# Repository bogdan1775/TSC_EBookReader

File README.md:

### Croitoru Constantin-Bogdan 334CA
# Proiect TSC

## Diagrama Bloc

## Bill Of Materials
| Nume | Link componenta | Link Datasheet |
|----------------|----------------|----------------|		
|	BOOT_BUTTON	|	https://www.snapeda.com/parts/EVQP7L01P/Panasonic/view-part/?welcome=home&ref=search&t=evqp7l01p	|	https://industry.panasonic.com/global/en/downloads?tab=catalog&small_g_cd=203&part_no=EVQPUJ02K	|
|	C1	|	https://componentsearchengine.com/part-view/CC0402MRX5R5BB106/YAGEO	|	https://componentsearchengine.com/Datasheets/2/CC0402MRX5R5BB106.pdf	|
|	C1_BAT	|	https://componentsearchengine.com/part-view/CC0402MRX5R5BB106/YAGEO	|	https://componentsearchengine.com/Datasheets/2/CC0402MRX5R5BB106.pdf	|
|	C1_BAT1	|	https://www.snapeda.com/parts/CC0402DRNPO9BN5R1/Yageo/view-part/?ref=dk&t=LTSPICE_CC0402&con_ref=None	|	https://s3.amazonaws.com/snapeda/datasheet/CC0402DRNPO9BN5R1_Yageo.pdf	|
|	C2_BAT1	|	https://www.snapeda.com/parts/CC0402DRNPO9BN5R1/Yageo/view-part/?ref=dk&t=LTSPICE_CC0402&con_ref=None	|	https://s3.amazonaws.com/snapeda/datasheet/CC0402DRNPO9BN5R1_Yageo.pdf	|
|	C1_BAT2	| https://www.snapeda.com/parts/CC0402DRNPO9BN5R1/Yageo/view-part/?ref=dk&t=LTSPICE_CC0402&con_ref=None	|	https://s3.amazonaws.com/snapeda/datasheet/CC0402DRNPO9BN5R1_Yageo.pdf	|
|	C2	|	https://componentsearchengine.com/part-view/CC0402MRX5R5BB106/YAGEO	|	https://componentsearchengine.com/Datasheets/2/CC0402MRX5R5BB106.pdf	|
|	C2_BAT	|	https://componentsearchengine.com/part-view/CC0402MRX5R5BB106/YAGEO	|	https://componentsearchengine.com/Datasheets/2/CC0402MRX5R5BB106.pdf	|
|	C3	|	https://componentsearchengine.com/part-view/T491B107M006AT/KEMET	|	https://s3.amazonaws.com/snapeda/datasheet/TAJB475K025RNJ_AVX.pdf	|
|	C4	|	https://componentsearchengine.com/part-view/CC0402MRX5R5BB106/YAGEO	|	https://componentsearchengine.com/Datasheets/2/CC0402MRX5R5BB106.pdf	|
|	C4_USB	|	https://componentsearchengine.com/part-view/CC0402MRX5R5BB106/YAGEO	|	https://componentsearchengine.com/Datasheets/2/CC0402MRX5R5BB106.pdf	|
|	C5	|	https://componentsearchengine.com/part-view/CC0402MRX5R5BB106/YAGEO	|	https://componentsearchengine.com/Datasheets/2/CC0402MRX5R5BB106.pdf	|
|	C5_USB	|	https://componentsearchengine.com/part-view/CC0402MRX5R5BB106/YAGEO	|	https://componentsearchengine.com/Datasheets/2/CC0402MRX5R5BB106.pdf	|
|	C6	|	https://componentsearchengine.com/part-view/CC0402MRX5R5BB106/YAGEO	|	https://componentsearchengine.com/Datasheets/2/CC0402MRX5R5BB106.pdf	|
|	C7	|	https://componentsearchengine.com/part-view/CC0402MRX5R5BB106/YAGEO	|	https://componentsearchengine.com/Datasheets/2/CC0402MRX5R5BB106.pdf	|
|	C8	|	https://componentsearchengine.com/part-view/CC0402MRX5R5BB106/YAGEO	|	https://componentsearchengine.com/Datasheets/2/CC0402MRX5R5BB106.pdf	|
|	C9	|	https://www.snapeda.com/parts/CC0402DRNPO9BN5R1/Yageo/view-part/?ref=dk&t=LTSPICE_CC0402&con_ref=None	|	https://s3.amazonaws.com/snapeda/datasheet/CC0402DRNPO9BN5R1_Yageo.pdf	|
|	C10	|	https://componentsearchengine.com/part-view/CC0402MRX5R5BB106/YAGEO	|	https://componentsearchengine.com/Datasheets/2/CC0402MRX5R5BB106.pdf	|
|	C10_SUPERCAP	|	https://www.snapeda.com/parts/CPH3225A/Seiko+Instruments/view-part/?ref=eda	|	https://www.snapeda.com/parts/CPH3225A/Seiko%20Instruments/datasheet/	|
|	CHANGE_BUTTON	|	https://www.snapeda.com/parts/EVQP7L01P/Panasonic/view-part/?welcome=home&ref=search&t=evqp7l01p	|	https://industry.panasonic.com/global/en/downloads?tab=catalog&small_g_cd=203&part_no=EVQPUJ02K	|
|	CHG_LED	|	https://www.snapeda.com/parts/KP-1608SURCK/Kingbright/view-part/?ref=search&t=LED%200603	|	https://www.snapeda.com/parts/KP-1608SURCK/Kingbright/datasheet/	|
|	C_DELAY	|	https://componentsearchengine.com/part-view/CC0402MRX5R5BB106/YAGEO	|	https://componentsearchengine.com/Datasheets/2/CC0402MRX5R5BB106.pdf	|
|	D1	|	https://www.snapeda.com/parts/USBLC6-2SC6Y/STMicroelectronics/view-part/?ref=snap	|	https://www.snapeda.com/parts/USBLC6-2SC6Y/STMicroelectronics/datasheet/	|
|	D2	|	https://ro.mouser.com/ProductDetail/KYOCERA-AVX/SD0805S020S1R0?qs=jCA%252BPfw4LHbpkAoSnwrdjw%3D%3D	|	http://datasheets.avx.com/schottky.pdf	|
|	D3	|	https://www.snapeda.com/parts/MBR0530/Onsemi/view-part/?ref=eda	|	https://www.snapeda.com/parts/MBR0530/ON%20Semiconductor/datasheet/	|
|	D4	|	https://www.snapeda.com/parts/MBR0530/Onsemi/view-part/?ref=eda	|	https://www.snapeda.com/parts/MBR0530/ON%20Semiconductor/datasheet/	|
|	D5	|	https://www.snapeda.com/parts/MBR0530/Onsemi/view-part/?ref=eda	|	https://www.snapeda.com/parts/MBR0530/ON%20Semiconductor/datasheet/	|
|	D6	|	https://www.snapeda.com/parts/PGB1010603MR/Littelfuse/view-part/?ref=eda	|	https://www.snapeda.com/parts/PGB1010603MR/Littelfuse%20Inc./datasheet/	|
|	D7	|	https://ro.mouser.com/ProductDetail/KYOCERA-AVX/SD0805S020S1R0?qs=jCA%252BPfw4LHbpkAoSnwrdjw%3D%3D	|	http://datasheets.avx.com/schottky.pdf	|
|	D8	|	https://www.snapeda.com/parts/PGB1010603MR/Littelfuse/view-part/?ref=eda	|	https://www.snapeda.com/parts/PGB1010603MR/Littelfuse%20Inc./datasheet/	|
|	D9	|	https://www.snapeda.com/parts/PGB1010603MR/Littelfuse/view-part/?ref=eda	|	https://www.snapeda.com/parts/PGB1010603MR/Littelfuse%20Inc./datasheet/	|
|	D10	|	https://www.snapeda.com/parts/PGB1010603MR/Littelfuse/view-part/?ref=eda	|	https://www.snapeda.com/parts/PGB1010603MR/Littelfuse%20Inc./datasheet/	|
|	D11	|	https://www.snapeda.com/parts/PGB1010603MR/Littelfuse/view-part/?ref=eda	|	https://www.snapeda.com/parts/PGB1010603MR/Littelfuse%20Inc./datasheet/	|
|	D12	|	https://www.snapeda.com/parts/PGB1010603MR/Littelfuse/view-part/?ref=eda	|	https://www.snapeda.com/parts/PGB1010603MR/Littelfuse%20Inc./datasheet/	|
|	EPD_C1	|	https://componentsearchengine.com/part-view/CC0402MRX5R5BB106/YAGEO	|	https://componentsearchengine.com/Datasheets/2/CC0402MRX5R5BB106.pdf	|
|	EPD_C2	|	https://componentsearchengine.com/part-view/CC0402MRX5R5BB106/YAGEO	|	https://componentsearchengine.com/Datasheets/2/CC0402MRX5R5BB106.pdf	|
|	EPD_C5	|	https://componentsearchengine.com/part-view/CC0402MRX5R5BB106/YAGEO	|	https://componentsearchengine.com/Datasheets/2/CC0402MRX5R5BB106.pdf	|
|	EPD_C6	|	https://componentsearchengine.com/part-view/CC0402MRX5R5BB106/YAGEO	|	https://componentsearchengine.com/Datasheets/2/CC0402MRX5R5BB106.pdf	|
|	EPD_C7	|	https://componentsearchengine.com/part-view/CC0402MRX5R5BB106/YAGEO	|	https://componentsearchengine.com/Datasheets/2/CC0402MRX5R5BB106.pdf	|
|	EPD_C8	|	https://componentsearchengine.com/part-view/CC0402MRX5R5BB106/YAGEO	|	https://componentsearchengine.com/Datasheets/2/CC0402MRX5R5BB106.pdf	|
|	EPD_C9	|	https://componentsearchengine.com/part-view/CC0402MRX5R5BB106/YAGEO	|	https://componentsearchengine.com/Datasheets/2/CC0402MRX5R5BB106.pdf	|
|	EPD_C10	|	https://componentsearchengine.com/part-view/CC0402MRX5R5BB106/YAGEO	|	https://componentsearchengine.com/Datasheets/2/CC0402MRX5R5BB106.pdf	|
|	EPD_C11	|	https://componentsearchengine.com/part-view/CC0402MRX5R5BB106/YAGEO	|	https://componentsearchengine.com/Datasheets/2/CC0402MRX5R5BB106.pdf	|
|	EPD_C12	|	https://componentsearchengine.com/part-view/CC0402MRX5R5BB106/YAGEO	|	https://componentsearchengine.com/Datasheets/2/CC0402MRX5R5BB106.pdf	|
|	IC1	|	https://componentsearchengine.com/part-view/BD5229G-TR/ROHM%20Semiconductor	|	https://datasheet.datasheetarchive.com/originals/distributors/Datasheets_SAMA/f2b9741ef86007909f138d561a359946.pdf	|
|	IC4	|	https://componentsearchengine.com/part-view/XC6220A331MR-G/Torex	|	https://product.torexsemi.com/system/files/series/xc6220.pdf	|
|	J1	|	https://componentsearchengine.com/part-view/FH34SRJ-24S-0.5SH(99)/Hirose	|	https://www.hirose.com/en/product/document?clcode=CL0580-1255-6-99&productname=FH34SRJ-24S-0.5SH(99)&series=FH34SRJ&documenttype=2DDrawing&lang=en&documentid=0000990903	|
|	J2	|	https://componentsearchengine.com/part-view/USB4110-GF-A/GCT%20(GLOBAL%20CONNECTOR%20TECHNOLOGY)	|	https://gct.co/files/drawings/usb4110.pdf	|
|	J3	|	https://componentsearchengine.com/part-view/SM04B-SRSS-TB(LF)(SN)/JST%20(JAPAN%20SOLDERLESS%20TERMINALS)	| - |
|	J4	|	https://store.comet.srl.ro/Catalogue/Product/43497/	|	https://store.comet.srl.ro/Catalogue/Product/43497/	|
|	L1	|	https://ro.mouser.com/ProductDetail/Wurth-Elektronik/744043680?qs=PGXP4M47uW6VkZq%252BkzjrHA%3D%3D	|	https://www.we-online.com/components/products/datasheet/744043680.pdf	|
|	PFMF.050.1	|	https://ro.mouser.com/ProductDetail/EPCOS-TDK/B72520T0350K062?qs=dEfas%2FXlABIszF52uu7vrg%3D%3D	|	https://www.mouser.co.uk/ProductDetail/EPCOS-TDK/B72520T0350K062?qs=dEfas%2FXlABIszF52uu7vrg%3D%3D	|
|	Q1	|	https://componentsearchengine.com/part-view/DMG2305UX-7/Diodes%20Incorporated	|	https://www.diodes.com//assets/Datasheets/DMG2305UX.pdf	|
|	Q2	|	https://componentsearchengine.com/part-view/DMG2305UX-7/Diodes%20Incorporated	|	https://www.diodes.com//assets/Datasheets/DMG2305UX.pdf	|
|	Q3	|	https://componentsearchengine.com/part-view/SI1308EDL-T1-GE3/Vishay	|	https://componentsearchengine.com/Datasheets/1/SI1308EDL-T1-GE3.pdf	|
|	R1	|	https://componentsearchengine.com/part-view/R0402%201%25%20100%20K%20(RC0402FR-07100KL)/YAGEO	|	https://www.yageo.com/upload/media/product/products/datasheet/rchip/PYu-RC_Group_51_RoHS_L_12.pdf	|
|	R1-PINH	|	https://componentsearchengine.com/part-view/R0402%201%25%20100%20K%20(RC0402FR-07100KL)/YAGEO	|	https://www.yageo.com/upload/media/product/products/datasheet/rchip/PYu-RC_Group_51_RoHS_L_12.pdf	|
|	R1-PINH1	|	https://componentsearchengine.com/part-view/R0402%201%25%20100%20K%20(RC0402FR-07100KL)/YAGEO	|	https://www.yageo.com/upload/media/product/products/datasheet/rchip/PYu-RC_Group_51_RoHS_L_12.pdf	|
|	R1_BAT	|	https://componentsearchengine.com/part-view/R0402%201%25%20100%20K%20(RC0402FR-07100KL)/YAGEO	|	https://www.yageo.com/upload/media/product/products/datasheet/rchip/PYu-RC_Group_51_RoHS_L_12.pdf	|
|	R1_PWRUSB	|	https://componentsearchengine.com/part-view/R0402%201%25%20100%20K%20(RC0402FR-07100KL)/YAGEO	|	https://www.yageo.com/upload/media/product/products/datasheet/rchip/PYu-RC_Group_51_RoHS_L_12.pdf	|
|	R2	|	https://componentsearchengine.com/part-view/R0402%201%25%20100%20K%20(RC0402FR-07100KL)/YAGEO	|	https://www.yageo.com/upload/media/product/products/datasheet/rchip/PYu-RC_Group_51_RoHS_L_12.pdf	|
|	R2-PINH	|	https://componentsearchengine.com/part-view/R0402%201%25%20100%20K%20(RC0402FR-07100KL)/YAGEO	|	https://www.yageo.com/upload/media/product/products/datasheet/rchip/PYu-RC_Group_51_RoHS_L_12.pdf	|
|	R2-PINH1	|	https://componentsearchengine.com/part-view/R0402%201%25%20100%20K%20(RC0402FR-07100KL)/YAGEO	|	https://www.yageo.com/upload/media/product/products/datasheet/rchip/PYu-RC_Group_51_RoHS_L_12.pdf	|
|	R2-USB	|	https://componentsearchengine.com/part-view/R0402%201%25%20100%20K%20(RC0402FR-07100KL)/YAGEO	|	https://www.yageo.com/upload/media/product/products/datasheet/rchip/PYu-RC_Group_51_RoHS_L_12.pdf	|
|	R2-USB1	|	https://componentsearchengine.com/part-view/R0402%201%25%20100%20K%20(RC0402FR-07100KL)/YAGEO	|	https://www.yageo.com/upload/media/product/products/datasheet/rchip/PYu-RC_Group_51_RoHS_L_12.pdf	|
|	R2_BAT	|	https://componentsearchengine.com/part-view/R0402%201%25%20100%20K%20(RC0402FR-07100KL)/YAGEO	|	https://www.yageo.com/upload/media/product/products/datasheet/rchip/PYu-RC_Group_51_RoHS_L_12.pdf	|
|	R3	|	https://componentsearchengine.com/part-view/R0402%201%25%20100%20K%20(RC0402FR-07100KL)/YAGEO	|	https://www.yageo.com/upload/media/product/products/datasheet/rchip/PYu-RC_Group_51_RoHS_L_12.pdf	|
|	R4	|	https://componentsearchengine.com/part-view/R0402%201%25%20100%20K%20(RC0402FR-07100KL)/YAGEO	|	https://www.yageo.com/upload/media/product/products/datasheet/rchip/PYu-RC_Group_51_RoHS_L_12.pdf	|
|	R5	|	https://componentsearchengine.com/part-view/R0402%201%25%20100%20K%20(RC0402FR-07100KL)/YAGEO	|	https://www.yageo.com/upload/media/product/products/datasheet/rchip/PYu-RC_Group_51_RoHS_L_12.pdf	|
|	R6	|	https://componentsearchengine.com/part-view/R0402%201%25%20100%20K%20(RC0402FR-07100KL)/YAGEO	|	https://www.yageo.com/upload/media/product/products/datasheet/rchip/PYu-RC_Group_51_RoHS_L_12.pdf	|
|	R7	|	https://componentsearchengine.com/part-view/R0402%201%25%20100%20K%20(RC0402FR-07100KL)/YAGEO	|	https://www.yageo.com/upload/media/product/products/datasheet/rchip/PYu-RC_Group_51_RoHS_L_12.pdf	|
|	R8	|	https://componentsearchengine.com/part-view/R0402%201%25%20100%20K%20(RC0402FR-07100KL)/YAGEO	|	https://www.yageo.com/upload/media/product/products/datasheet/rchip/PYu-RC_Group_51_RoHS_L_12.pdf	|
|	R9	|	https://componentsearchengine.com/part-view/R0402%201%25%20100%20K%20(RC0402FR-07100KL)/YAGEO	|	https://www.yageo.com/upload/media/product/products/datasheet/rchip/PYu-RC_Group_51_RoHS_L_12.pdf	|
|	R10	|	https://componentsearchengine.com/part-view/R0402%201%25%20100%20K%20(RC0402FR-07100KL)/YAGEO	|	https://www.yageo.com/upload/media/product/products/datasheet/rchip/PYu-RC_Group_51_RoHS_L_12.pdf	|
|	RESET_BUTTON	|	https://www.snapeda.com/parts/EVQP7L01P/Panasonic/view-part/?welcome=home&ref=search&t=evqp7l01p	|	https://industry.panasonic.com/global/en/downloads?tab=catalog&small_g_cd=203&part_no=EVQPUJ02K	|
|	R_BOOT	|	https://componentsearchengine.com/part-view/R0402%201%25%20100%20K%20(RC0402FR-07100KL)/YAGEO	|	https://www.yageo.com/upload/media/product/products/datasheet/rchip/PYu-RC_Group_51_RoHS_L_12.pdf	|
|	R_CAPACITOR	|	https://componentsearchengine.com/part-view/R0402%201%25%20100%20K%20(RC0402FR-07100KL)/YAGEO	|	https://www.yageo.com/upload/media/product/products/datasheet/rchip/PYu-RC_Group_51_RoHS_L_12.pdf	|
|	R_CHANGE	|	https://componentsearchengine.com/part-view/R0402%201%25%20100%20K%20(RC0402FR-07100KL)/YAGEO	|	https://www.yageo.com/upload/media/product/products/datasheet/rchip/PYu-RC_Group_51_RoHS_L_12.pdf	|
|	R_CL1	|	https://componentsearchengine.com/part-view/R0402%201%25%20100%20K%20(RC0402FR-07100KL)/YAGEO	|	https://www.yageo.com/upload/media/product/products/datasheet/rchip/PYu-RC_Group_51_RoHS_L_12.pdf	|
|	R_RESET	|	https://componentsearchengine.com/part-view/R0402%201%25%20100%20K%20(RC0402FR-07100KL)/YAGEO	|	https://www.yageo.com/upload/media/product/products/datasheet/rchip/PYu-RC_Group_51_RoHS_L_12.pdf	|
|	SENSOR2	|	https://www.snapeda.com/parts/BME680/Bosch/view-part/?welcome=home	|	https://www.snapeda.com/parts/BME680/Bosch%20Sensortec/datasheet/	|
|	SJ1	|	https://grabcad.com/library/solder-jumpers-1	|	https://www.digikey.com/en/htmldatasheets/production/1809569/0/0/1/jumpers	|
|	U1	|	https://www.snapeda.com/parts/W25Q512JVEIQ/Winbond+Electronics/view-part/?ref=eda	|	https://www.snapeda.com/parts/W25Q512JVEIQ/Winbond%20Electronics/datasheet/	|
|	U2	|	https://www.snapeda.com/parts/ESP32-C6-WROOM-1-N8/Espressif+Systems/view-part/?ref=eda	|	https://www.snapeda.com/parts/ESP32-C6-WROOM-1-N8/Espressif%20Systems/datasheet/	|
|	U3	|	https://www.snapeda.com/parts/DS3231SN%23/Analog%20Devices/view-part/?ref=dk&t=DS3231SN%23&con_ref=None	|	https://www.snapeda.com/parts/DS3231SN%23/Analog%20Devices/datasheet/	|
|	U4	|	https://www.snapeda.com/parts/MAX17048G+T10/Analog+Devices/view-part/?ref=eda	|	https://www.snapeda.com/parts/MAX17048G+T10/Analog%20Devices/datasheet/	|
|	U5	|	https://ro.mouser.com/ProductDetail/Microchip-Technology/MCP73831T-2ACI-OT?qs=yUQqVecv4qvbBQBGbHx0Mw%3D%3D	|	https://ro.mouser.com/datasheet/2/268/MCP73831_Family_Data_Sheet_DS20001984H-3441711.pdf	|
|	TP1	|		|		|
|	TP2	|		|		|
|	TP3	|		|		|
|	TP4	|		|		|
|	TP5	|		|		|
|	TP6	|		|		|
|	TP7	|		|		|
|	TP8	|		|		|
|	TP9	|		|		|
|	TP10	|		|		|
|	TP11	|		|		|
|	TP12	|		|		|
|	TP13	|		|		|
|	TP14	|		|		|
|	TP15	|		|		|
|	TP16	|		|		|
|	TP17	|		|		|

## Descriere functionalitate
Dispozitivul este construit in jurul microcontrolerului ESP32-C6, care serveste ca unitate centrala de procesare si interactioneaza cu diverse componente esentiale pentru funcționarea sa.

Pentru a asigura o urmarire precisa a timpului, dispozitivul include un modul RTC DS3231SN, care comunica cu ESP32-C6 prin interfata I2C, garantand sincronizarea corecta a datelor si evenimentelor.

Senzorul de mediu BME680 este responsabil pentru colectarea informatiilor despre mediul înconjurator. Acesta transmite datele catre microcontroler prin I2C.

Dispozitivul beneficiaza si de un slot pentru card SD, utilizat pentru stocarea datelor colectate sau a altor informatii relevante. Acesta comunica cu ESP32-C6 prin interfata SPI, asigurand o stocare externa eficienta. De asemenea, exista o memorie Flash NOR externa de 64MB (W25Q512JVIQ) pentru stocarea firmware-ului si a altor date persistente.

Afisarea datelor si a altor informatii vizuale se realizeaza printr-un display E-Paper, care este conectat la ESP32-C6 prin pini GPIO dedicati.

In ceea ce priveste alimentarea, dispozitivul utilizeaza un conector USB-C (SAMACSYS_PARTS_USB4110-GF-A) cu protectie ESD, iar incarcarea bateriei Li-Po este gestionata de un controller de incarcare MCP73831. Un stabilizator de tensiune LDO (XC6220A331MR-G) asigura o alimentare stabila, iar nivelul de incarcare al bateriei este monitorizat cu ajutorul unui circuit MAX17048G+T.

Comunicarea intre componentele dispozitivului se face eficient datorita unui conector Qwiic (QWIIC_CONNECTORJS-1MM), care faciliteaza conectarea rapida a dispozitivelor I2C între ele.

In total, dispozitivul este un sistem complet si portabil, alimentat de o baterie Li-Po, cu conectivitate USB-C, care integreaza un microcontroler ESP32-C6, senzori pentru monitorizarea mediului, un RTC pentru urmarirea timpului si o solutie de stocare extinsa, toate interconectate prin interfetele I2C si SPI.

## Pini folositi
Modulul DS3231SN RTC si senzorul BME688: ambii folosesc pinii GPIO19 (SDA) si GPIO20 (SCL) pentru comunicarea I2C, un protocol serial pentru transferul de date.
Cardul SD: Comunica prin SPI, folosind pinii GPIO7 (MOSI), GPIO27 (MISO), GPIO4 (SS_SD) si GPIO6 (SCK) pentru transferul de date si sincronizare.
Display-ul E-Paper: Utilizeaza pini specifici pentru control: GPIO18 (EPD_3V3_C), GPIO11 (EPD_CS), GPIO5 (EPD_DC), GPIO21 (EPD_RST) si GPIO26 (EPD_BUSY).
Butoane: Pinii GPIO3 (RESET), GPIO15 (IO/BOOT) si GPIO23 (IO/CHANGE) sunt folositi pentru detectarea actiunilor utilizatorului, cum ar fi resetarea sau intrarea in modul de boot.

## Rezolvare Warnings
Am dat approve warning-urilor de tip Power de la schema electrica.
Am dat approve warningului "Pin A2 connected to VBUS".

## Rezolvare Errors
Am dat approve erorilor de la componenta J2.
Am rezolvat erorile de la Bobina L1 prin modificarea pad-urilor .
Am rezolvat erorile de la componenta U4.

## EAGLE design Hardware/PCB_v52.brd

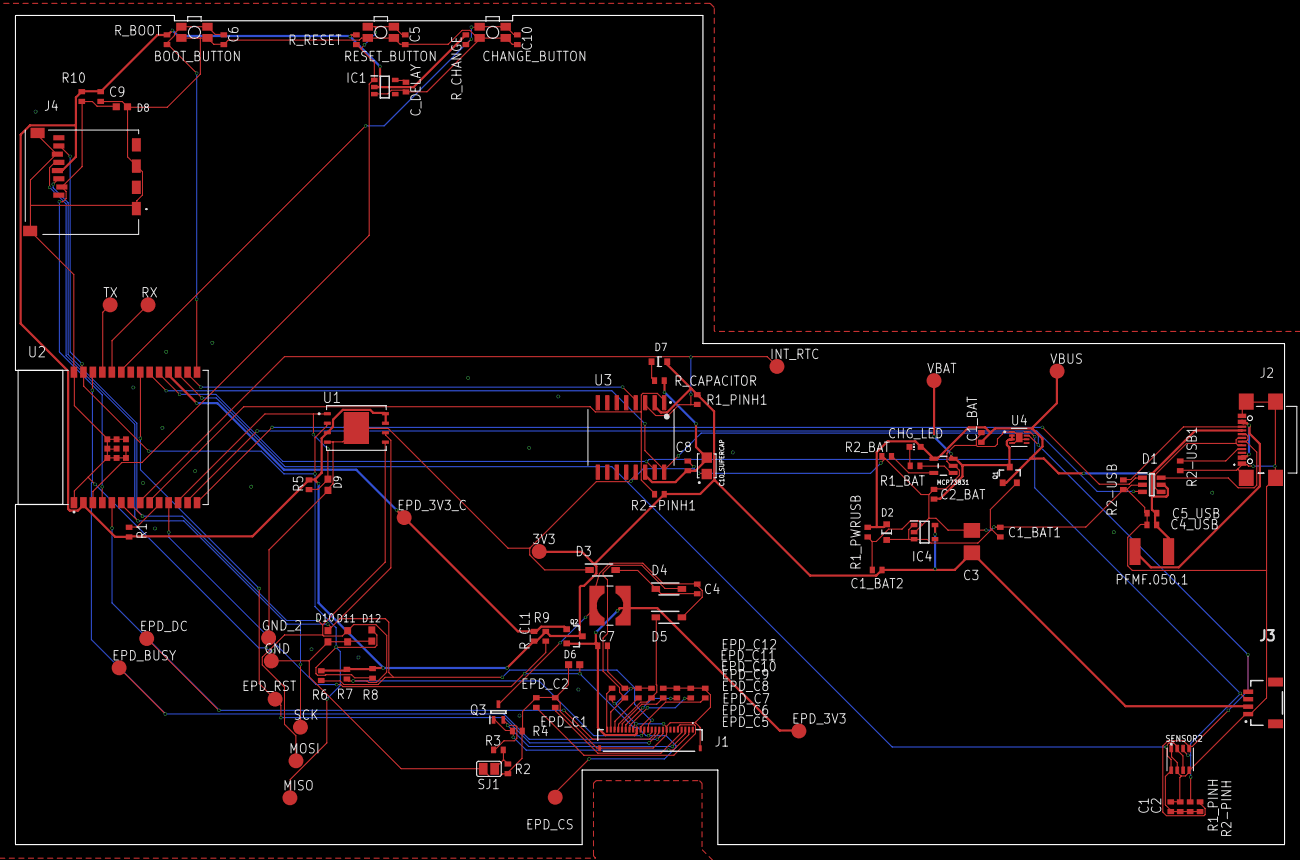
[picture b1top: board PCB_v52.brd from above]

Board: 2 copper layers, 170.2 x 111.2 mm, 103 parts (0 on the bottom side), 56 nets.

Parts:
3V3: TPTP20R; TP20R
BOOT_BUTTON: BUTTON_CUSYOMV1; MYBUTTON
C1, C2, C4_USB, C6, C8, C9, C10: 100nF; EAGLE-LTSPICE_C0402
C1_BAT, C1_BAT1, C1_BAT2, C2_BAT, C5_USB: 4.7uF; EAGLE-LTSPICE_C0402
C3: 100uF TANT; RCL_CT3528
C4: 4.7uF/25V; EAGLE-LTSPICE_C0402
C5: 1uF; EAGLE-LTSPICE_C0402
C7: 10uF; EAGLE-LTSPICE_C0402
C10_SUPERCAP: CPH3225A; CAPCP3225X100N
CHANGE_BUTTON: BUTTON_CUSYOMV1; MYBUTTON
CHG_LED: ADAFRUIT_CHIP-LED0603
C_DELAY: 100nF; EAGLE-LTSPICE_C0402
D1: USBLC6-2SC6Y; SOT95P280X145-6N
D2, D7: ESP32_WROVER_AVX---SD0805S020S1R0_AVX_SD0805S020S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; ESP32_WROVER_AVX---SD0805S020S1R0_AVX_SD0805S020S1R0_0
D3, D4, D5: MBR0530; SOD3716X135N
D6, D8, D9, D10, D11, D12: PGB1010603MR; DIOC1608X36N
EPD_3V3, EPD_3V3_C: TPTP20R; TP20R
EPD_BUSY: TPTP20R; TP20R
EPD_C1, EPD_C2, EPD_C6, EPD_C7, EPD_C8, EPD_C9, EPD_C10, EPD_C11, EPD_C12: 1uF/50V; EAGLE-LTSPICE_C0402
EPD_C5: 0.1uF/50V; EAGLE-LTSPICE_C0402
EPD_CS: TPTP20R; TP20R
EPD_DC: TPTP20R; TP20R
EPD_RST: TPTP20R; TP20R
GND: TPTP20R; TP20R
GND_2: TPTP20R; TP20R
IC1: BD5229G-TR; SOT95P280X125-5N
IC4: XC6220A331MR-G; SOT95P280X120-5N
INT_RTC: TPTP20R; TP20R
J1: FH34SRJ-24S-0.5SH_99_; FH34SRJ24S05SH99
J2: SAMACSYS_PARTS_USB4110-GF-A; SAMACSYS_PARTS_USB4110GFA
J3: QWIIC_RIGHT_ANGLE; JST04_1MM_RA
J4: 112A-TAAR-R03_ATTEND; 112ATAARR03ATTEND
L1: 68uH; IND_4828-WE-TPC_WRE
MCP73831: ESP32_WROVER_SPARKFUN-IC-POWER_MCP73831; ESP32_WROVER_SPARKFUN-IC-POWER_SOT23-5
MISO: TPTP20R; TP20R
MOSI: TPTP20R; TP20R
PFMF.050.1: ESP32C6_VARISTORCN1812; ESP32C6_VARISTOR_CT/CN1812
Q1, Q2: 20V/4.2A/52mΩ/1.4W; ESP32_WROVER_SPARKFUN-DISCRETESEMI_SOT23-3
Q3: SI1308EDL-T1-GE3; SOT65P210X110-3N
R1, R1_PINH, R1_PINH1, R2-PINH, R2-PINH1, R4: 10k; ESP32_WROVER_EAGLE-LTSPICE_R0402
R1_BAT: 200; ESP32_WROVER_EAGLE-LTSPICE_R0402
R1_PWRUSB: 100k; ESP32_WROVER_EAGLE-LTSPICE_R0402
R2: 2.2; ESP32_WROVER_EAGLE-LTSPICE_R0402
R2-USB: 5k1; ESP32_WROVER_EAGLE-LTSPICE_R0402
R2-USB1: 5K1; ESP32_WROVER_EAGLE-LTSPICE_R0402
R2_BAT: 2k; ESP32_WROVER_EAGLE-LTSPICE_R0402
R3: 0.47; ESP32_WROVER_EAGLE-LTSPICE_R0402
R5, R6, R7, R8, R9, R10: 10K; ESP32_WROVER_EAGLE-LTSPICE_R0402
RESET_BUTTON: BUTTON_CUSYOMV1; MYBUTTON
RX: TPTP20R; TP20R
R_BOOT: 10k; ESP32_WROVER_EAGLE-LTSPICE_R0402
R_CAPACITOR: 15; ESP32_WROVER_EAGLE-LTSPICE_R0402
R_CHANGE: 10k; ESP32_WROVER_EAGLE-LTSPICE_R0402
R_CL1: 10k; ESP32_WROVER_EAGLE-LTSPICE_R0402
R_RESET: 10k; ESP32_WROVER_EAGLE-LTSPICE_R0402
SCK: TPTP20R; TP20R
SENSOR2: ESP32_WROVER_BME680_BME680; ESP32_WROVER_BME680_PSON80P300X300X100-8N
SJ1: SJ
TX: TPTP20R; TP20R
U1: W25Q512JVEIQ; SON127P600X800X80-9N
U2: ESP32-C6-WROOM-1-N8; XCVR_ESP32-C6-WROOM-1-N8
U3: DS3231SN#; SOIC127P1032X265-16N
U4: MAX17048G+T10; SON50P200X200X80-9N
VBAT: TPTP20R; TP20R
VBUS: TPTP20R; TP20R

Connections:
3V3: 3V3.TP, C1_BAT2.1, C3.+, C9.1, D7.2, IC1.2, IC4.5, J3.2, J4.P4, Q2.3, R1.2, R1_PINH1.2, R2-PINH1.2, R5.2, R6.2, R7.2, R8.2, R9.2, R10.2, R_BOOT.2, R_CHANGE.2, R_CL1.2, R_RESET.2, U1.3, U1.7, U1.8, U2.2, U3.2
32KHZ: R2-PINH1.1, U2.9, U3.1
DN: D1.4, J2.A7, J2.B7
DP: D1.6, J2.A6, J2.B6
EPD_3V3: C7.1, EPD_3V3.TP, J1.16, L1.2, Q2.2
EPD_3V3_C: EPD_3V3_C.TP, Q2.1, R_CL1.1, U2.18
EPD_BUSY: EPD_BUSY.TP, J1.9, U2.26
EPD_CS: D6.2, EPD_CS.TP, J1.12, R9.1, U2.11
EPD_DC: EPD_DC.TP, J1.11, U2.5
EPD_RST: EPD_RST.TP, J1.10, U2.21
FLASH_CS: D9.2, R5.1, U1.1, U2.12
GDR: J1.2, Q3.1, R4.2
GND: BOOT_BUTTON.1, BOOT_BUTTON.2, C1.2, C1_BAT.2, C1_BAT1.2, C1_BAT2.2, C2.2, C2_BAT.2, C3.-, C4_USB.2, C5.2, C5_USB.2, C6.2, C7.2, C8.2, C9.2, C10.2, C10_SUPERCAP.1, CHANGE_BUTTON.1, CHANGE_BUTTON.2, C_DELAY.2, D1.2, D3.1, D6.1, D8.1, D9.1, D10.1, D11.1, D12.1, EPD_C1.2, EPD_C2.2, EPD_C5.2, EPD_C6.2, EPD_C7.2, EPD_C8.2, EPD_C9.2, EPD_C10.2, EPD_C11.2, EPD_C12.1, GND.TP, GND_2.TP, IC1.3, IC4.2, J1.8, J1.17, J1.MP1, J1.MP2, J2.A1, J2.A12, J2.B1, J2.B12, J2.MP1, J2.MP2, J2.MP3, J2.MP4, J3.1, J4.G1, J4.G2, J4.G3, J4.G4, J4.P6, MCP73831.2, R1_PWRUSB.1, R2.1, R2-USB.2, R2-USB1.1, R2_BAT.1, R4.1, RESET_BUTTON.1, RESET_BUTTON.2, SENSOR2.1, SENSOR2.5, SENSOR2.7, SJ1.1, U1.4, U1.9, U2.1, U2.28, U2.29_1, U2.29_2, U2.29_3, U2.29_4, U2.29_5, U2.29_6, U2.29_7, U2.29_8, U2.29_9, U3.13, U4.1, U4.4, U4.6, U4.9
GPIO8: R1.1, U2.10
I2C_PW: C1.1, C2.1, R1_PINH.2, R2-PINH.2, SENSOR2.2, SENSOR2.6, SENSOR2.8, U2.17
INT_RTC: INT_RTC.TP, R1_PINH1.1, U2.8, U3.3
IO/BOOT: BOOT_BUTTON.3, BOOT_BUTTON.4, C6.1, R_BOOT.1, U2.15
IO/CHANGE: C10.1, CHANGE_BUTTON.3, CHANGE_BUTTON.4, R_CHANGE.1, U2.23
MISO: D12.2, J4.P7, MISO.TP, R8.1, U1.2, U2.27
MOSI: D11.2, J1.14, J4.P3, MOSI.TP, R7.1, U1.5, U2.7
unnamed: C_DELAY.1, IC1.5
unnamed: J2.B5, R2-USB.1
unnamed: J2.A5, R2-USB1.2
unnamed: D7.1, R_CAPACITOR.1
unnamed: C1_BAT1.1, D2.1, IC4.1, IC4.3, Q1.2
unnamed: MCP73831.1, R1_BAT.2
unnamed: CHG_LED.C, R1_BAT.1
unnamed: C4.1, D3.2, D4.1
unnamed: MCP73831.5, R2_BAT.2
unnamed: EPD_C12.2, J1.24
unnamed: EPD_C10.1, J1.22
unnamed: EPD_C8.1, J1.20
unnamed: EPD_C7.1, J1.19
unnamed: EPD_C6.1, J1.18
unnamed: EPD_C5.1, J1.15
unnamed: EPD_C1.1, J1.4
unnamed: EPD_C2.1, J1.5
PREVGH: D5.1, EPD_C9.1, J1.21
PREVGL: D4.2, EPD_C11.1, J1.23
RESE: J1.3, Q3.2, R3.2
RESE': R2.2, R3.1, SJ1.2
RESET: C5.1, IC1.1, RESET_BUTTON.3, RESET_BUTTON.4, R_RESET.1, U2.3
RTC_RST: U2.16, U3.4
RX: RX.TP, U2.24
SCK: D10.2, J1.13, J4.P5, R6.1, SCK.TP, U1.6, U2.6
SCL: J3.4, R2-PINH.1, SENSOR2.4, U2.20, U3.16, U4.7
SDA: J3.3, R1_PINH.1, SENSOR2.3, U2.19, U3.15, U4.8
SRC: C4.2, D5.2, L1.1, Q3.3
SS_SD: D8.2, J4.P2, R10.1, U2.4
TX: TX.TP, U2.25
USB_D+: D1.1, U2.14
USB_D-: D1.3, U2.13
VBAT: C2_BAT.1, MCP73831.3, Q1.3, U4.2, U4.3, VBAT.TP
VBUS: C1_BAT.1, C4_USB.1, C5_USB.1, CHG_LED.A, D1.5, D2.2, J2.A8, MCP73831.4, PFMF.050.1.2, Q1.1, R1_PWRUSB.2, VBUS.TP
VRTC: C8.1, C10_SUPERCAP.2, R_CAPACITOR.2, U3.14
VUSB: J2.A4, J2.A9, J2.B4, J2.B9, PFMF.050.1.1

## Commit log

2025-04-06 Create vvv
2025-04-06 Create LICENSE

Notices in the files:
parts and their libraries:
COPYRIGHT: Copyright (C) 2024 Ultra Librarian. All rights reserved.
